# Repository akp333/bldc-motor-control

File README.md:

# BLDC Motor Controller (Arduino, PI Control and Custom PCB)

Sensored 6-step BLDC motor control built around an Arduino and three IR2112 half-bridge gate drivers. It covers open-loop speed control, closed-loop PI speed control, hardware overcurrent protection and a KiCad PCB layout. The simulation was done in Proteus.

| Stage | What it does | Tools |
|---|---|---|
| **PS-1** | Open-loop Hall-sensor commutation, CW/CCW switching, overcurrent cutoff | Proteus, Arduino |
| **PS-2** | Closed-loop PI speed control (200–500 RPM) | Proteus, Arduino |
| **Bonus** | 2-layer power-stage PCB with current-rated traces | KiCad |

## Hardware

- **Power stage:** 3 half-bridges (6 N-MOSFETs) driven by 3x IR2112. Each phase has a bootstrap diode and capacitor so the high-side gate can be driven to VS + 12 V.
- **Sensing:** 3 Hall sensors with 1k pull-ups give rotor position.
- **Overcurrent protection:** a single 0.1 Ω shunt on the shared low-side return feeds a comparator. Only 2 phases conduct at a time, so one shunt sees the total current. The comparator trips an Arduino input, which turns every MOSFET off.
- **Controls:** a potentiometer sets speed and a button toggles direction.

## PS-1: Open-Loop Control

- Found the Hall code for each of the 6 commutation steps experimentally. I forced each step, read the Hall bits, and noticed that the two values seen per step correspond to CW vs CCW.
- Added a manual 6-step startup kick, because the motor can't self-start from Hall feedback alone.
- Mapped the pot to the delay between commutation steps. This targeted RPM much more predictably than PWM duty did, with slight oscillation about the target.
- Overcurrent trips immediately and all gates go low. RPM then coasts down slowly because the simulation has little friction.

## PS-2: Closed-Loop PI Control

- The pot sets a target of 200–500 RPM. Measured RPM is computed from the time between Hall transitions, and the PI controller adjusts PWM duty on the high-side switches.
- Hall transitions stood in for a rotary encoder, since Proteus has no encoder compatible with this motor model. This gives only 6 updates per electrical revolution, so resolution is lower.
- Integral control reduces steady-state error.
- The accumulated error is capped to prevent overshoot.
- Kp = 2, Ki = 1.2, tuned by hand along with motor friction and load.

| Target | Overshoot | Settled at |
|---|---|---|
| 200 RPM | ~15 RPM | ~190–195 RPM |
| 500 RPM | none | ~490 RPM |

The residual steady-state error is a deliberate trade-off. Raising Ki further caused overshoot, oscillation and Proteus "timestep too small" errors. Less overshoot at 500 RPM is likely because friction rises with speed.

## Bonus: PCB (KiCad)

- Reused the PS-1 power and comparator schematic. The motor, Hall sensors and button are brought out to headers, and the comparator Vref comes from a fixed voltage divider instead of a pot.
- Connectors: J1 (+12 V / +5 V), J2 (3-phase motor output), J3 (8-pin Arduino interface).
- Ran ERC (added PWR_FLAGs and the LM393 supply pins), assigned footprints, and routed the board in 2 layers on 80 x 80 mm.
- **Trace sizing:** the sustained current measured in simulation was ~7 A, which needs ~2.2 mm width at a 10 °C rise using the KiCad calculator. 1 oz copper made this too wide to route, so I switched to **2 oz (70 µm)**. Signal traces use the default width.
- A ~8 A transient spike was ignored for sizing, since trace heating depends on sustained rather than instantaneous current.
- DRC passed and the board was checked in 3D view.

## Known Limitations

- Simulation only, no hardware build or physical testing.
- Tuning is specific to the 200–500 RPM range and the load and friction I set in Proteus.
- Single pole-pair motor assumed in the RPM calculation (`POLE_PAIRS = 1`).
- Footprints for PCB were chosen from online research and not checked against real component availability.

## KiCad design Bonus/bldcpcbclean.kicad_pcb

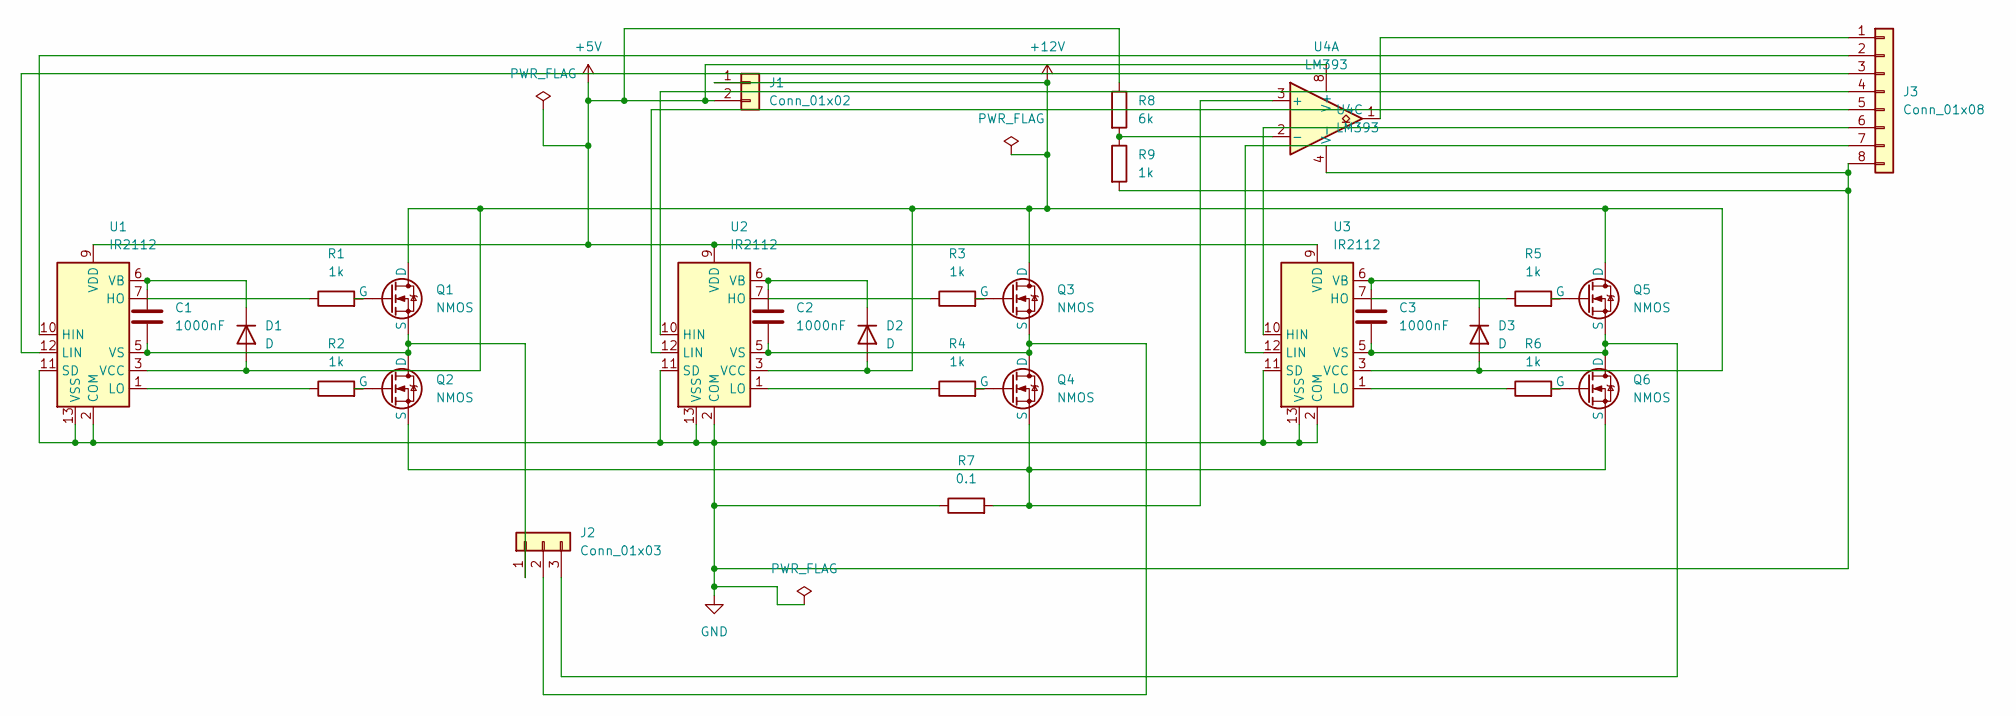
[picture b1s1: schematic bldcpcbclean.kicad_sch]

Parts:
C1, C2, C3: 1000nF; C_Disc_D5.0mm_W2.5mm_P5.00mm
D1, D2, D3: D; D_DO-35_SOD27_P7.62mm_Horizontal
J1: Conn_01x02; PinHeader_1x02_P2.54mm_Vertical
J2: Conn_01x03; PinHeader_1x03_P2.54mm_Vertical
J3: Conn_01x08; PinHeader_1x08_P2.54mm_Vertical
Q1, Q2, Q3, Q4, Q5, Q6: NMOS; TO-220-3_Vertical
R1, R2, R3, R4, R5, R6, R9: 1k; R_Axial_DIN0207_L6.3mm_D2.5mm_P10.16mm_Horizontal
R7: 0.1; R_Axial_DIN0207_L6.3mm_D2.5mm_P10.16mm_Horizontal
R8: 6k; R_Axial_DIN0207_L6.3mm_D2.5mm_P10.16mm_Horizontal
U1, U2, U3: IR2112; DIP-14_W7.62mm
U4: LM393; DIP-8_W7.62mm

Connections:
+5V: J1.2, R8.1, U1.9 (VDD), U2.9 (VDD), U3.9 (VDD), U4.8 (V+)
+12V: D1.2 (A), D2.2 (A), D3.2 (A), J1.1, Q1.1 (D), Q3.1 (D), Q5.1 (D), U1.3 (VCC), U2.3 (VCC), U3.3 (VCC)
GND: J3.8, R7.1, R9.2, U1.2 (COM), U1.11 (SD), U1.13 (VSS), U2.2 (COM), U2.11 (SD), U2.13 (VSS), U3.2 (COM), U3.11 (SD), U3.13 (VSS), U4.4 (V-)
unnamed: C1.1, D1.1 (K), U1.6 (VB)
unnamed: C2.1, D2.1 (K), U2.6 (VB)
unnamed: C3.1, D3.1 (K), U3.6 (VB)
unnamed: C1.2, J2.1, Q1.3 (S), Q2.1 (D), U1.5 (VS)
unnamed: C2.2, J2.2, Q3.3 (S), Q4.1 (D), U2.5 (VS)
unnamed: C3.2, J2.3, Q5.3 (S), Q6.1 (D), U3.5 (VS)
unnamed: J3.1, U4.1
unnamed: J3.2, U1.10 (HIN)
unnamed: J3.3, U1.12 (LIN)
unnamed: J3.4, U2.10 (HIN)
unnamed: J3.5, U2.12 (LIN)
unnamed: J3.6, U3.10 (HIN)
unnamed: J3.7, U3.12 (LIN)
unnamed: Q1.2 (G), R1.2
unnamed: Q2.2 (G), R2.2
unnamed: Q2.3 (S), Q4.3 (S), Q6.3 (S), R7.2, U4.3 (+)
unnamed: Q3.2 (G), R3.2
unnamed: Q4.2 (G), R4.2
unnamed: Q5.2 (G), R5.2
unnamed: Q6.2 (G), R6.2
unnamed: R1.1, U1.7 (HO)
unnamed: R2.1, U1.1 (LO)
unnamed: R3.1, U2.7 (HO)
unnamed: R4.1, U2.1 (LO)
unnamed: R5.1, U3.7 (HO)
unnamed: R6.1, U3.1 (LO)
unnamed: R8.2, R9.1, U4.2 (-)

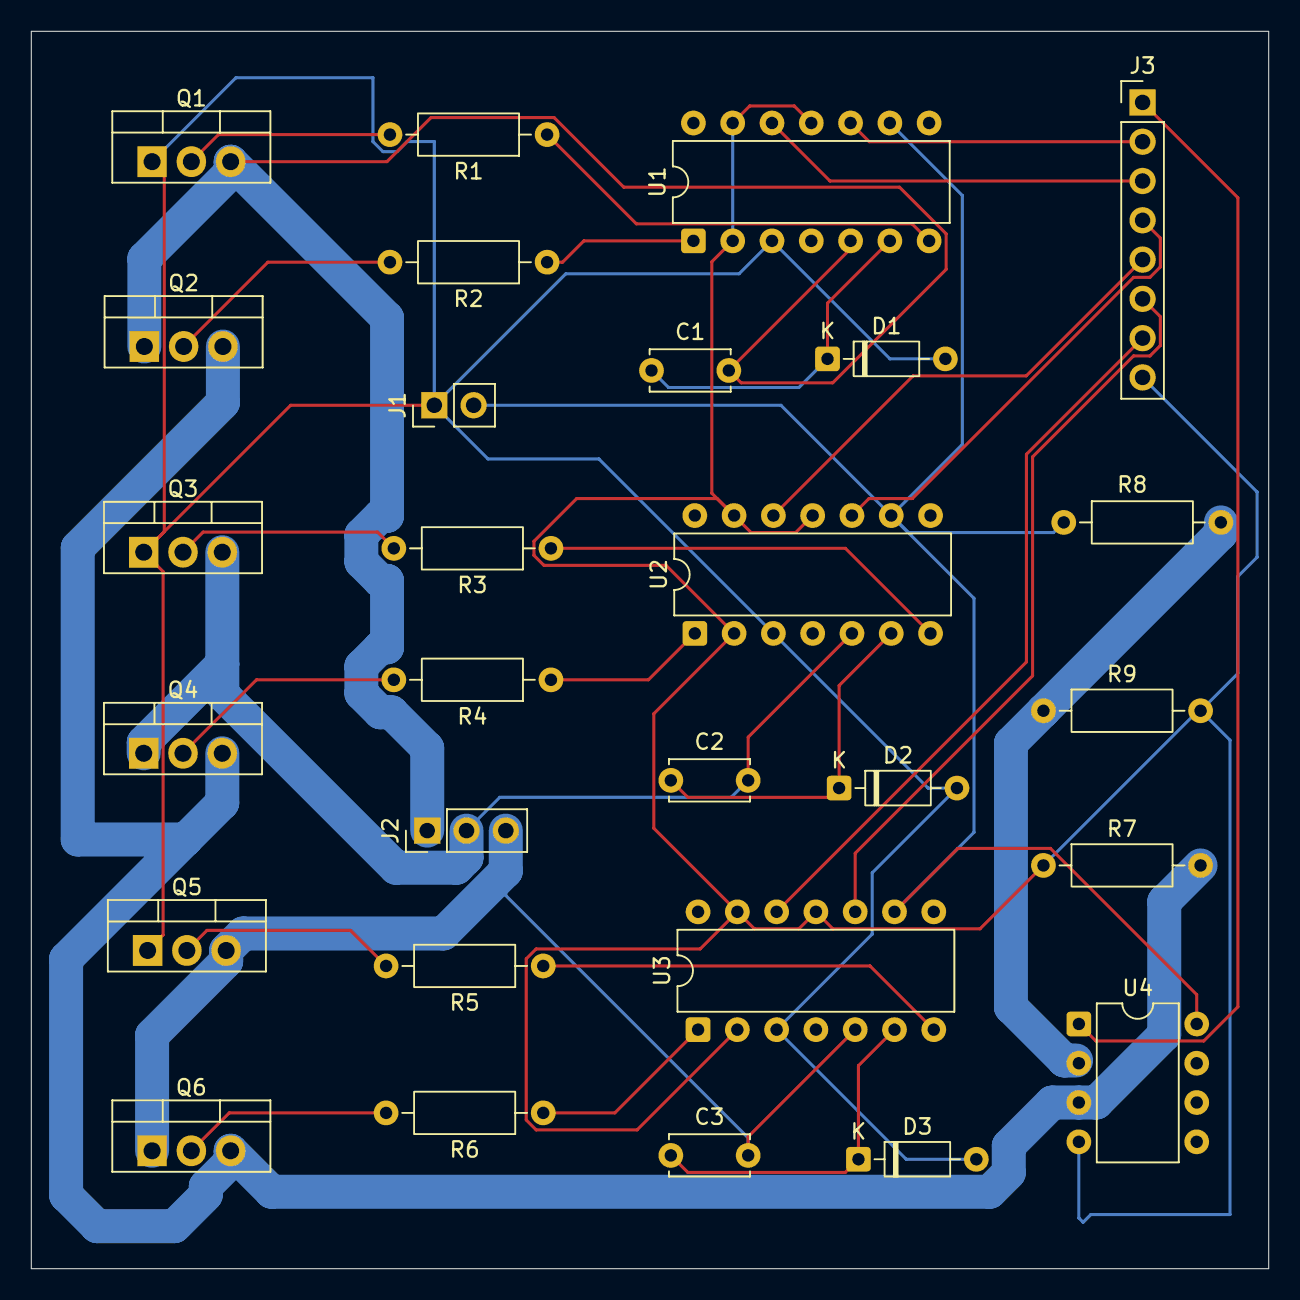
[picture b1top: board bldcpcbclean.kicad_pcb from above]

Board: 2 copper layers, 80.0 x 80.0 mm, 28 parts (0 on the bottom side), 30 nets.
